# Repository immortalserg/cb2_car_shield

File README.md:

# cb2 car shield

Шилд для Cubieboard2 (или Banana Pi M1, M1+, M3, M2M, R2, M64, M2 Ultra, M2 Berry, Nanopi A64) и LCD панели LQ123K1LG03 под этот шлейф (разъем J1) или этот шлейф (разъем J2)

### Разъемы для подключения LVDS

Omron XF2M-4015-1A - 40 контактный BananaPi M3, A64, M2B, M2U, R2 (разъем J4), M1, M1+ (разъем J5)

Omron XF2M-2415-1A - 24 контактный BananaPi M2M (разъем J3)

Omron XF2M-3015-1A - 30 контактный NanoPi A64 (разъем J6)

### Описание

Разъемы Omron применены для того, чтобы не задумываться над расположением разъема так как стандартные разъемы (например Hirose) имеют одностороннее подключение шлейфа в отличии от Omron у которого двухстороннее подключение шлейфа.

Миникомпьютер предназначен для вывода информации на экран, по уарт к миникомпьютеру подключен микроконтроллер Atmel SAM3X8E (Arduino DUE) который считывает данные и по uart передает на миникомпьютер , входы к микроконтроллеру подключены через буферы MC14503B (цифровые порты 22-52), цифровые порты 8-12 можно использовать как ШИМ и 53 как I/O запаяв перемычки или как входы запаяв микросхему. Аналоговые порты 0-7 для подключения датчиков через делители.

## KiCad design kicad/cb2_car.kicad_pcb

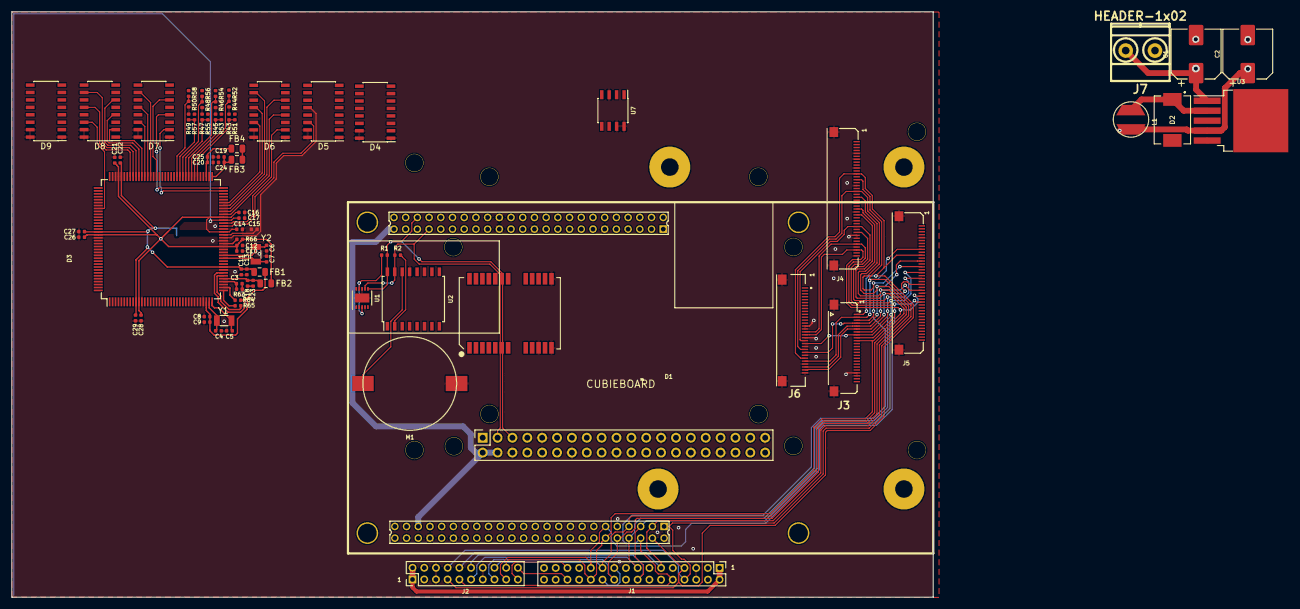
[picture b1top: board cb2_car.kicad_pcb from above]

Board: 2 copper layers, 157.4 x 100.0 mm, 82 parts (0 on the bottom side), 81 nets.

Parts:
AE1: ANTENNA; LQ123K1LG03
C1: 680 uF; CP_Elec_8x10
C2: 220 uF; CP_Elec_8x10
C3, C4, C5, C6, C7: 22 pF; C_0402_1005Metric
C8, C12, C13, C14, C15, C16, C17, C18, C19, C20, C21, C22, C26, C27, C28, C29: 100 nF; C_0402_1005Metric
C9, C10, C11, C23, C24, C25: 10 uF; C_0402_1005Metric
D1: BananaPi; BananaPi_m2m_v5
D2: SS34; DIOM7959X265
D3: ATSAM3X8EA-AU; LQFP-144_20x20mm_P0.5mm
D4, D5, D6, D7, D8, D9: MC14503B; SOIC-16_3.9x9.9mm_P1.27mm
FB1, FB2, FB3, FB4: MH2029-300Y; C_0805_2012Metric
J1: Conn_02x15_Odd_Even; PinHeader_2x16_P2.00mm_Vertical
J2: HEADER-2x10; PinHeader_2x10_P2.00mm_Vertical
J3: Omron XF2M-2415-1A; Omron_XF2M-2415-1A
J4, J5: Omron XF2M-4015-1A; Omron_XF2M-4015-1A
J6: Omron XF2M-3015-1A; Omron_XF2M-3015-1A
J7: HEADER-1x02; mkds_1,5-2
L1: 33 uH; CD54
M1: CR1220SMD; cr1220_smd
R1, R2: 4,7 K; R_0402_1005Metric
R43, R44, R45, R46, R47, R48, R49, R50: 47k; R_0402_1005Metric
R51, R52, R53, R54, R55, R56, R57, R58, R66: 100k; R_0402_1005Metric
R63: 6k8 1%; R_0402_1005Metric
R64, R65: 39R 1%; R_0402_1005Metric
U1: MMA7660FCR1_Obsolete; DFN-10-1EP_3x3mm_P0.5mm_EP1.55x2.48mm
U2: DS3231_SO; SOIC-16W_7.5x10.3mm_P1.27mm
U3: LM2596S-5; TO-263-5_TabPin3
U4: MOUDLE-GPS-NEO-6M(24P-16X12.2MM); Neo_GPS24P-SMD-1.1-16X12.2MM
U7: DS2482; SOIC-8_3.9x4.9mm_P1.27mm
X1: CUBIEBOARD; Cubieboard2
Y1: 12MHz; Crystal_SMD_3215-2Pin_3.2x1.5mm
Y2: 32.768Khz; Crystal_SMD_3215-2Pin_3.2x1.5mm

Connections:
+3.3V: C10.2, C12.2, C14.2, C16.2, C21.2, C26.2, C28.2, D3.11, D3.52, D3.57, D3.62, D3.105, D3.125, D4.8, D5.8, D6.8, D7.8, D8.8, D9.8, FB2.1, FB3.1, FB4.1, J1.1, J1.2, J2.1, J2.2, R1.1, R2.1, R66.2, U1.3, U1.9, U2.2
+5V: C2.1, D1.2, D1.4, L1.2, U3.4, U7.1, X1.43, X1.49
AVDREF: C20.2, C25.2, D3.75, FB4.2
GND: C1.2, C2.2, C3.1, C4.2, C5.2, C6.2, C7.2, C8.1, C9.1, C10.1, C11.1, C12.1, C13.1, C14.1, C15.1, C16.1, C17.1, C18.1, C19.1, C20.1, C21.1, C22.1, C23.1, C24.1, C25.1, C26.1, C27.1, C28.1, C29.1, D1.6, D1.9, D1.14, D1.20, D1.25, D1.30, D1.34, D1.39, D2.2, D3.12, D3.33, D3.44, D3.54, D3.58, D3.74, D3.106, D3.126, D4.1, D4.15, D4.16, D5.1, D5.15, D5.16, D6.1, D6.15, D6.16, D7.1, D7.15, D7.16, D8.1, D8.15, D8.16, D9.1, D9.15, D9.16, J1.5, J1.6, J1.9, J1.12, J1.19, J1.22, J2.5, J2.6, J2.13, J2.14, J3.21, J3.22, J3.25, J3.26, J4.5, J4.7, J4.10, J4.16, J4.22, J4.25, J4.28, J4.33, J4.34, J4.37, J4.40, J4.41, J4.42, J5.5, J5.24, J5.41, J5.42, J6.14, J6.15, J6.18, J6.21, J6.24, J6.27, J6.30, J6.31, J6.32, J7.1, M1.1, R43.1, R44.1, R45.1, R46.1, R47.1, R48.1, R49.1, R50.1, R63.2, U1.4, U1.8, U1.11, U2.13, U3.3, U3.5, U4.10, U4.12, U4.13, U7.3, U7.7, U7.8, X1.2, X1.9, X1.20, X1.38, X1.42, X1.67, X1.68, X1.73, X1.85
unnamed: C1.1, J7.2, U3.1
unnamed: C3.2, D3.40, R63.1
unnamed: C4.1, D3.35, Y1.1
unnamed: C5.1, D3.36, Y1.2
unnamed: C6.1, D3.49, Y2.1
unnamed: C7.1, D3.48, Y2.2
unnamed: C8.2, C9.2, D3.34, FB1.2
unnamed: D2.1, L1.1, U3.2
unnamed: D3.37, R65.2
unnamed: D3.38, R64.2
unnamed: D3.42, R65.1
unnamed: D3.43, R64.1
unnamed: D3.53, R66.1
unnamed: M1.2, U2.14
RL_UD: J1.27, J2.19
RX: D1.10, U4.20
RXCLK+: J1.21, J2.16, J3.6, J4.26, J5.21, J6.29, X1.7
RXCLK-: J1.20, J2.15, J3.5, J4.24, J5.23, J6.28, X1.10
RXIN0+: J1.8, J2.8, J3.2, J4.14, J5.9, J6.26, X1.1
RXIN0-: J1.7, J2.7, J3.1, J4.12, J5.11, J6.25, X1.4
RXIN1+: J1.11, J2.10, J3.4, J4.20, J5.13, J6.23, X1.3
RXIN1-: J1.10, J2.9, J3.3, J4.18, J5.15, J6.22, X1.6
RXIN2+: J1.16, J2.12, J3.8, J4.32, J5.17, J6.20, X1.5
RXIN2-: J1.15, J2.11, J3.7, J4.30, J5.19, J6.19, X1.8
RXIN3+: J1.24, J2.18, J3.10, J4.38, J5.25, J6.17, X1.12
RXIN3-: J1.23, J2.17, J3.9, J4.36, J5.27, J6.16, X1.11
SCL: D1.5, R1.2, U1.6, U2.16, X1.54
SDA: D1.3, R2.2, U1.7, U2.15, X1.55
SELLVDS: J1.28, J2.20
TX: D1.8, U4.21
VDDANA: C19.2, C24.2, D3.73, FB3.2
VDDOUT: C11.2, C13.2, C15.2, C17.2, C22.2, C27.2, C29.2, D3.10, D3.45, D3.56, D3.61, D3.104, D3.124, FB1.1
VDDUTMI: C18.2, C23.2, D3.41, FB2.2
a0: D3.78, R43.2, R51.2
a1: D3.79, R44.2, R52.2
a2: D3.80, R45.2, R53.2
a3: D3.81, R46.2, R54.2
a4: D3.82, R47.2, R55.2
a5: D3.83, R48.2, R56.2
a6: D3.84, R49.2, R57.2
a7: D3.85, R50.2, R58.2
d8: D3.133, D9.4
d9: D3.132, D9.6
d10: D3.111, D9.10
d11: D3.20, D9.14
d12: D3.21, D9.12
d23: D3.7, D4.2
d24: D3.8, D4.4
d25: D3.13, D4.6
d26: D3.14, D4.10
d27: D3.15, D4.12
d28: D3.16, D4.14
d29: D3.19, D5.2
d30: D3.22, D5.4
d31: D3.26, D5.6
d32: D3.32, D5.10
d33: D3.55, D5.12
d34: D3.59, D5.14
d35: D3.60, D6.2
d36: D3.116, D8.14
d37: D3.63, D6.4
d38: D3.64, D6.6
d39: D3.65, D6.10
d40: D3.66, D6.12
d41: D3.67, D6.14
d42: D3.71, D7.2
d43: D3.72, D7.4
d44: D3.101, D8.12
d45: D3.100, D8.10
d46: D3.99, D8.6
d47: D3.98, D8.4
d48: D3.97, D8.2
d49: D3.96, D7.14
d50: D3.95, D7.12
d51: D3.94, D7.10
d52: D3.92, D7.6
d53: D3.140, D9.2

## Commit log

2018-12-07 a msg
